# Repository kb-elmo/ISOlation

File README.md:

# ISOlation

[![CC BY-NC-SA 4.0][cc-by-nc-sa-shield]][cc-by-nc-sa]

### A seamless ISO single-key "macropad"
#### Stupid things I come up with during Covid isolation...

---

[STEP files for the case](case/)

[KiCAD PCB files](pcb/)

[Gerbers for PCB production](pcb/gerbers/)

[JLCPCB BOM](pcb/fab/iso_bom_jlc.csv)

[JLCPCB CPL](pcb/fab/iso_cpl_jlc.csv)

[Vial-QMK firmware](firmware/)

---

This work is licensed under a
[Creative Commons Attribution-NonCommercial-ShareAlike 4.0 International License][cc-by-nc-sa].

[![CC BY-NC-SA 4.0][cc-by-nc-sa-image]][cc-by-nc-sa]

[cc-by-nc-sa]: http://creativecommons.org/licenses/by-nc-sa/4.0/
[cc-by-nc-sa-image]: https://licensebuttons.net/l/by-nc-sa/4.0/88x31.png
[cc-by-nc-sa-shield]: https://img.shields.io/badge/License-CC%20BY--NC--SA%204.0-lightgrey.svg

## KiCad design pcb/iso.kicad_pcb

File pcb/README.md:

# ISOlation PCB

### Features

- Full key and stabilizer RGB
- Screw-in stabilizer support
- Powered by an Atmega328p
- Basic ESD and overvoltage protection
- Centered USB type-C port for a detachable cable
- Fully programmable using [QMK](https://qmk.fm) and [Vial](https://get.vial.today)

---

### Preview

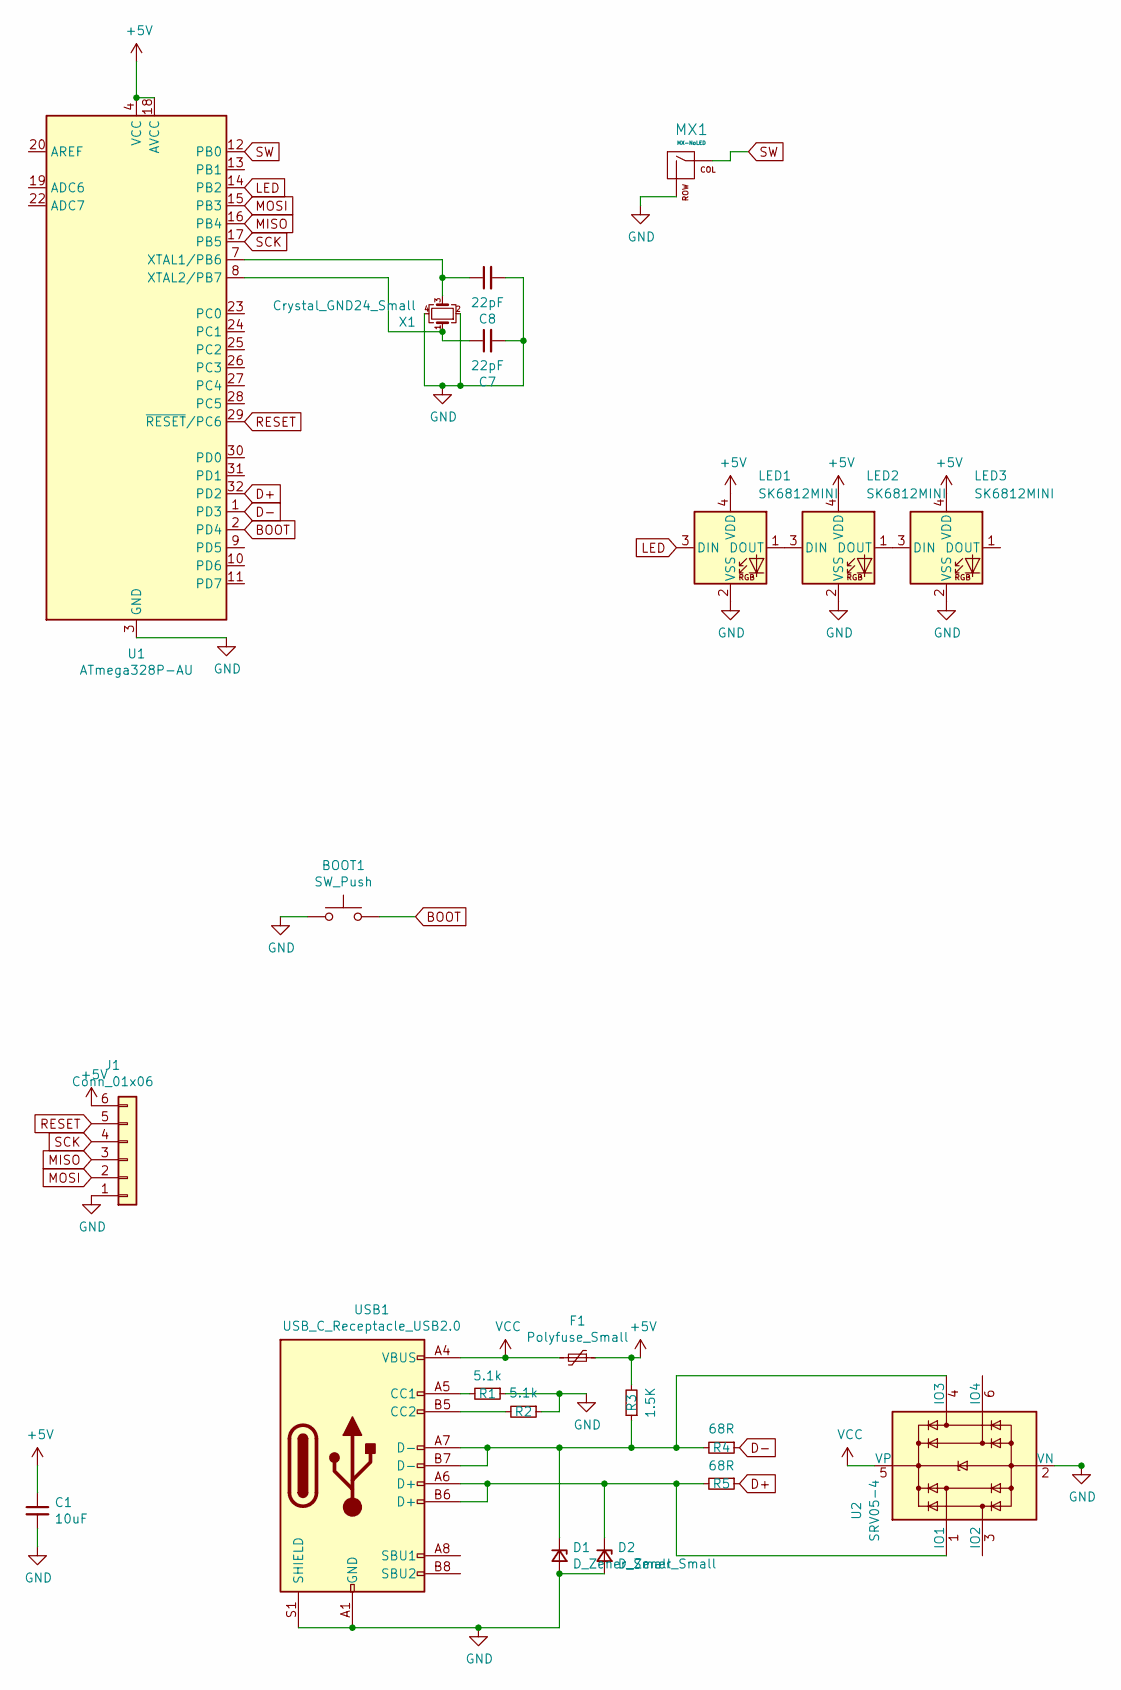
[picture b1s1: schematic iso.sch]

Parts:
BOOT1: SW_Push; PinHeader_1x02_P2.00mm_Vertical
C1: 10uF; C_0603_1608Metric; LCSC C19702
C7, C8: 22pF; C_0603_1608Metric; LCSC C1653
D1, D2: D_Zener_Small; D_SOD-323; LCSC C401091
F1: Polyfuse_Small; Fuse_1206_3216Metric; LCSC C69688
J1: Conn_01x06; PinHeader_1x06_P2.00mm_Vertical
LED1, LED2, LED3: SK6812MINI; SK6812MINIE-simple
MX1: MX-NoLED; MXOnly-ISO-ROTATEDCCW-ReversedStabilizers-NoLED
R1, R2: 5.1k; R_0603_1608Metric; LCSC C23186
R3: 1.5K; R_0603_1608Metric; LCSC C22843
R4, R5: 68R; R_0603_1608Metric; LCSC C27592
U1: ATmega328P-AU; TQFP-32_7x7mm_P0.8mm; LCSC C14877
U2: SRV05-4; SOT-23-6; LCSC C85364
USB1: USB_C_Receptacle_USB2.0; USB_C_Receptacle_HRO_TYPE-C-31-M-12; LCSC C165948
X1: Crystal_GND24_Small; Crystal_SMD_3225-4Pin_3.2x2.5mm; LCSC C13738

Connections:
+5V: C1.1, F1.1, J1.6, LED1.4 (VDD), LED2.4 (VDD), LED3.4 (VDD), R3.2, U1.4 (VCC), U1.6 (VCC), U1.18 (AVCC)
BOOT: BOOT1.2, U1.2 (PD4); also elsewhere on the board
D+: R5.1, U1.32 (PD2)
D-: R4.1, U1.1 (PD3)
GND: BOOT1.1, C1.2, C7.2, C8.2, D1.2 (A), D2.2 (A), J1.1, LED1.2 (VSS), LED2.2 (VSS), LED3.2 (VSS), MX1.2 (ROW), R1.1, R2.1, U1.3 (GND), U1.5 (GND), U1.21 (GND), U2.2 (VN), USB1.A1 (GND), USB1.A12 (GND), USB1.B1 (GND), USB1.B12 (GND), USB1.S1 (SHIELD), X1.2, X1.4; also elsewhere on the board
LED: LED1.3 (DIN), U1.14 (PB2)
MISO: J1.3, U1.16 (PB4)
MOSI: J1.2, U1.15 (PB3)
unnamed: C7.1, U1.8 (XTAL2/PB7), X1.1
unnamed: C8.1, U1.7 (XTAL1/PB6), X1.3
unnamed: D1.1 (K), R3.1, R4.2, U2.4 (IO3), USB1.A7 (D-), USB1.B7 (D-)
unnamed: D2.1 (K), R5.2, U2.1 (IO1), USB1.A6 (D+), USB1.B6 (D+)
unnamed: LED1.1 (DOUT), LED2.3 (DIN)
unnamed: LED2.1 (DOUT), LED3.3 (DIN)
unnamed: R1.2, USB1.A5 (CC1)
unnamed: R2.2, USB1.B5 (CC2)
RESET: J1.5, U1.29 (~RESET~/PC6)
SCK: J1.4, U1.17 (PB5)
SW: MX1.1 (COL), U1.12 (PB0)
VCC: F1.2, U2.5 (VP), USB1.A4 (VBUS), USB1.A9 (VBUS), USB1.B4 (VBUS), USB1.B9 (VBUS)

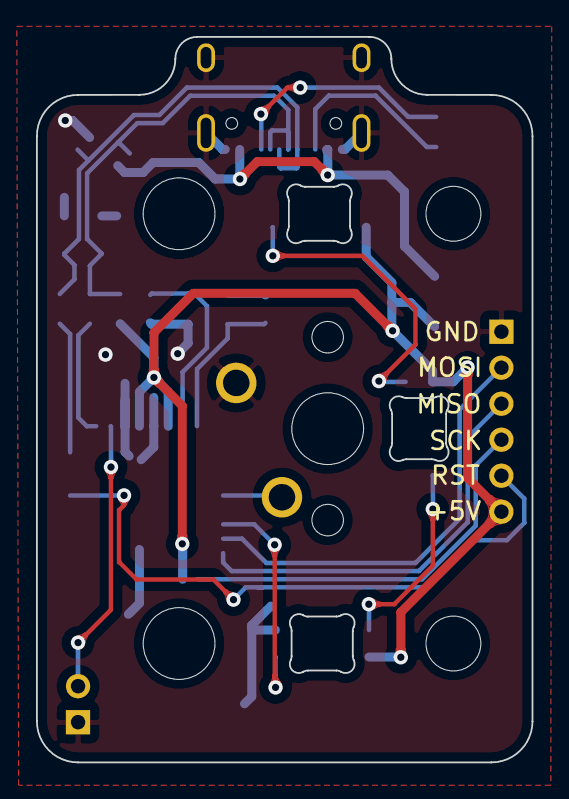
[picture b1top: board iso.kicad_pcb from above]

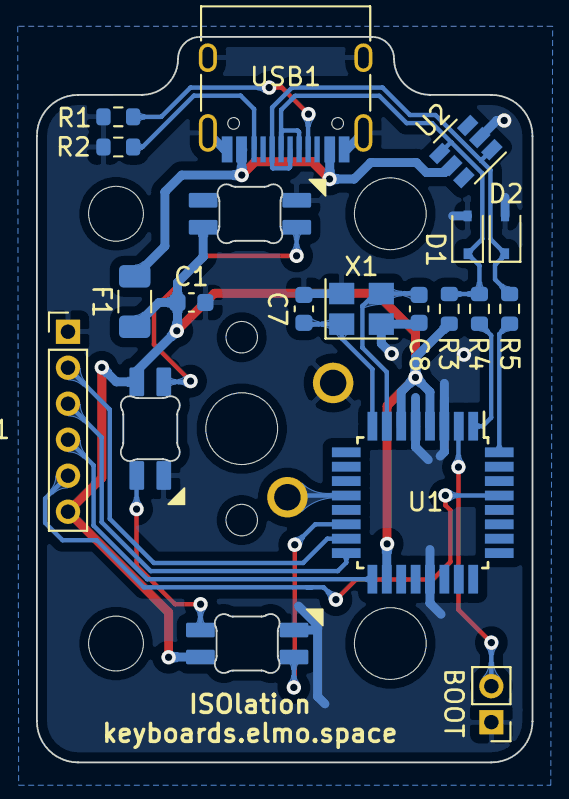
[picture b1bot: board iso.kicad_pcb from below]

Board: 2 copper layers, 27.5 x 40.3 mm, 21 parts (17 on the bottom side), 20 nets.

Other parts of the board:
BOOT: SW_Push; PinHeader_1x02_P2.00mm_Vertical

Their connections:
BOOT: BOOT.2; also elsewhere on the board
GND: BOOT.1; also elsewhere on the board

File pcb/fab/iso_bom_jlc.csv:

"Comment","Designator","Footprint","LCSC Part #"
"10uF","C1","C_0603_1608Metric","C19702"
"22pF","C7,C8","C_0603_1608Metric","C1653"
"D_Zener_Small","D2,D1","D_SOD-323","C401091"
"Polyfuse_Small","F1","Fuse_1206_3216Metric","C69688"
"5.1k","R1,R2","R_0603_1608Metric","C23186"
"1.5K","R3","R_0603_1608Metric","C22843"
"68R","R4,R5","R_0603_1608Metric","C27592"
"ATmega328P-AU","U1","TQFP-32_7x7mm_P0.8mm","C14877"
"SRV05-4","U2","SOT-23-6","C85364"
"USB_C_Receptacle_USB2.0","USB1","USB_C_Receptacle_HRO_TYPE-C-31-M-12","C165948"
"Crystal_GND24_Small","X1","Crystal_SMD_3225-4Pin_3.2x2.5mm","C13738"

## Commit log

2021-09-22 RGB!!!
2021-09-23 update images
2021-09-29 added firmware
2021-10-06 update firmware
2024-02-15 add bootloader firmware
2024-02-22 fix and update bootloader firmware
2024-02-22 update vial-qmk firmware files
2024-02-22 add precompiled vial firmware file
